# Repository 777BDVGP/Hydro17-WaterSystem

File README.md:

# Hydro17 Water System — borehole, tank, irrigation & pool controller

A home water controller on a **WEMOS LOLIN S2 Mini** (ESP32-S2): it fills a water
tank from a borehole, runs up to **9 irrigation zones** on **6 solenoid valves**,
drives the tank filter pump, and switches the **pool filter pump**, **pool light**
and a **plugs relay** on schedules. It can skip watering after rain by asking a
[Rain Gauge](https://777bdvgp.github.io/RainGauge/). Everything is a web page on
your own WiFi — no cloud, no app.

**Install / update page:** https://777bdvgp.github.io/Hydro17-WaterSystem/

**Contents:** [Features](#features) · [Hardware](#hardware) · [Pin map](#pin-map) ·
[Installing the firmware](#installing-the-firmware) · [First start: WiFi](#first-start-wifi) ·
[Rain gauge](#rain-gauge) · [Updating](#updating) ·
[Building the firmware yourself](#building-the-firmware-yourself) · [Licence](#licence)

> **Who this is for:** someone with hands-on experience in electronics and
> irrigation plumbing. It is not a kit manual. The guide grows over time —
> parts marked **(to be completed)** get more detail and photos later.

## Features

- **HOME** — live status: tank level, float switches, borehole pump, valves,
  active irrigation zone, pool pump and light, maintenance due dates.
- **Irrigation** — 9 zones, each with its own valve configuration, start date /
  time, duration, every-N-days frequency, water source (tank or borehole),
  per-weekday suspend, manual or scheduled mode; a 7-day suspend calendar.
- **Rain gauge** (optional) — asks a Rain Gauge on the same network every hour
  whether to irrigate today; zones set to "Respect Rainfall" are skipped when it
  says no. Gauge not reachable for 3 hours = irrigate as normal.
- **Tank** — fill by float switch or level sensor, any time or inside a time
  window, start / stop levels, filter pump delay after filling.
- **Pool** — filter pump 7-day schedule with manual override, pool light on / off.
- **Valves** — names for the valves and 9 valve configurations.
- **Manual operation** — switch the controller off (all automatic logic stops),
  with automatic return to normal after a set time.
- **NTFY** — free push alerts on your phone ([ntfy.sh](https://ntfy.sh)), e.g.
  maintenance due dates.
- **Reports** — general, irrigation and tank-filling logs.
- **WiFi** — saved networks list (add / delete, passwords never shown), joins the
  strongest network in range and the **strongest access point** when several
  share one WiFi name (mesh / multi-AP). Setup hotspot **Hydro17-Setup** for a new
  board or when no network can be reached.
- **ABOUT** — **firmware update from GitHub** (CHECK / INSTALL) or from an uploaded `.bin`.
- **Safety** — software watchdog, gateway keepalive ping (reboots after 5 min
  without the router), low-memory guard, optional nightly reboot.

## Hardware

- WEMOS LOLIN S2 Mini (ESP32-S2, 4 MB flash, 2 MB PSRAM).
- Main PCB: Eagle files in [`PCB/`](PCB) (`WEMOS_ESP32_2S_V5.sch` / `.brd`).
  Gerbers **(to be completed)**.
- Float / relay board: `ManualFloatRelaysV2.sch` / `.brd` and its Gerber ZIP
  [`ManualFloatRelaysV2_2024-05-08.zip`](PCB/ManualFloatRelaysV2_2024-05-08.zip).
- Relay / driver outputs for the solenoid valves, borehole pump, tank filter
  pump, pool pump, pool light and plugs; inputs for float switches and the
  panel buttons / switches; analogue tank level sensor.
- Bill of materials, wiring and photos **(to be completed)**.

## Pin map

| Output | GPIO | | Input | GPIO |
|---|---|---|---|---|
| Tank supply solenoid | 4 | | Tank level sensor (ADC) | 1 |
| Irrigation valve 1 | 5 | | Pool filter sensor (ADC) | 2 |
| Irrigation valve 2 | 6 | | Tank filter sensor (ADC) | 3 |
| Irrigation valve 3 | 7 | | Tank filter on / off button | 33 |
| Irrigation valve 4 | 8 | | Controller disable / enable button | 34 |
| Irrigation valve 5 | 9 | | Pool filter switch | 35 |
| Irrigation valve 6 | 10 | | Pool light switch | 36 |
| Borehole pump relay | 11 | | Plugs on / off switch | 37 |
| Controller disabled LED | 12 | | Tank high float switch | 38 |
| Tank low LED | 13 | | Tank low float switch | 39 |
| Tank high LED | 14 | | BOOT button (WiFi setup) | 0 |
| Pool light relay | 16 | | | |
| Pool filter pump relay | 17 | | | |
| Plugs relay | 18 | | | |
| Tank filter pump relay | 21 | | | |
| Tank fill solenoid | 40 | | | |

## Installing the firmware

No PlatformIO needed: open **https://777bdvgp.github.io/Hydro17-WaterSystem/** in
Chrome or Edge on a PC, plug the S2 Mini in with a USB **data** cable and press
**CONNECT**. Choose **Erase** for a new board, then **Install**. If no port shows
up, hold **0**, tap **RST**, release **0** and try again (tap **RST** once more
after the install).

## First start: WiFi

1. A new controller opens its own hotspot **Hydro17-Setup** (the LED blinks fast).
2. Connect a phone to it — the setup page opens by itself (otherwise browse to `http://192.168.4.1/`).
3. Pick your network, type the password and give it a **fixed IP**, press **SAVE & RESTART**.
4. Put the phone back on your WiFi and open the fixed IP (or `http://hydro17.local/`).

More networks: **SETTINGS → WiFi Networks**. Hold **BOOT** or the **CONTROLLER**
button while powering up to open the setup hotspot again. If no saved network can
be reached for about 4 minutes, the hotspot opens by itself for 5 minutes, then
the controller restarts and tries again.

## Rain gauge

On **SETTINGS** tick **Use Rain Gauge** and enter the gauge's IP (e.g.
`192.168.1.124`). The controller asks `http://<gauge>/api/irrigate` every hour (and
right after saving); the badge under the settings shows **IRRIGATE** (green) or
**NO IRRIGATION TODAY** (red). Only zones with **Respect Rainfall = Yes** are
skipped.

## Updating

On the **ABOUT** page: **CHECK FOR UPDATE** compares the version with the one on the
install page; **INSTALL FROM GITHUB** downloads and installs it (not while a zone
irrigates or the borehole pump runs). Settings and logs are kept; a failed
download leaves the old firmware running. Without internet at the controller:
download [`hydro17.bin`](docs/firmware/hydro17.bin) and use **UPLOAD & INSTALL**.

## Building the firmware yourself

[PlatformIO](https://platformio.org/) project in [`Hydro17/`](Hydro17):

```bash
cd Hydro17
pio run -e usb -t upload                                   # first flash over USB
pio run -e ota -t upload --upload-port <controller ip>     # later over WiFi
```

`main.cpp` is the single translation unit — it `#include`s every module, so every
cross-file function needs a declaration in `src/00_ForwardDecl.h`.

Optional built-in WiFi networks: copy `src/wifi_secrets.example.h` to
`src/wifi_secrets.h` (git-ignored). Builds with that file are named `_PRIVATE` —
do not share them, your passwords are inside.

## Licence

[CC BY-NC 4.0](LICENSE) — free for personal use, not for sale. No warranty: this
controls pumps, valves and pool equipment, and they run on mains power — have
mains wiring done or checked by a qualified person.

Copyright (c) 2026 Bennie Vermeulen

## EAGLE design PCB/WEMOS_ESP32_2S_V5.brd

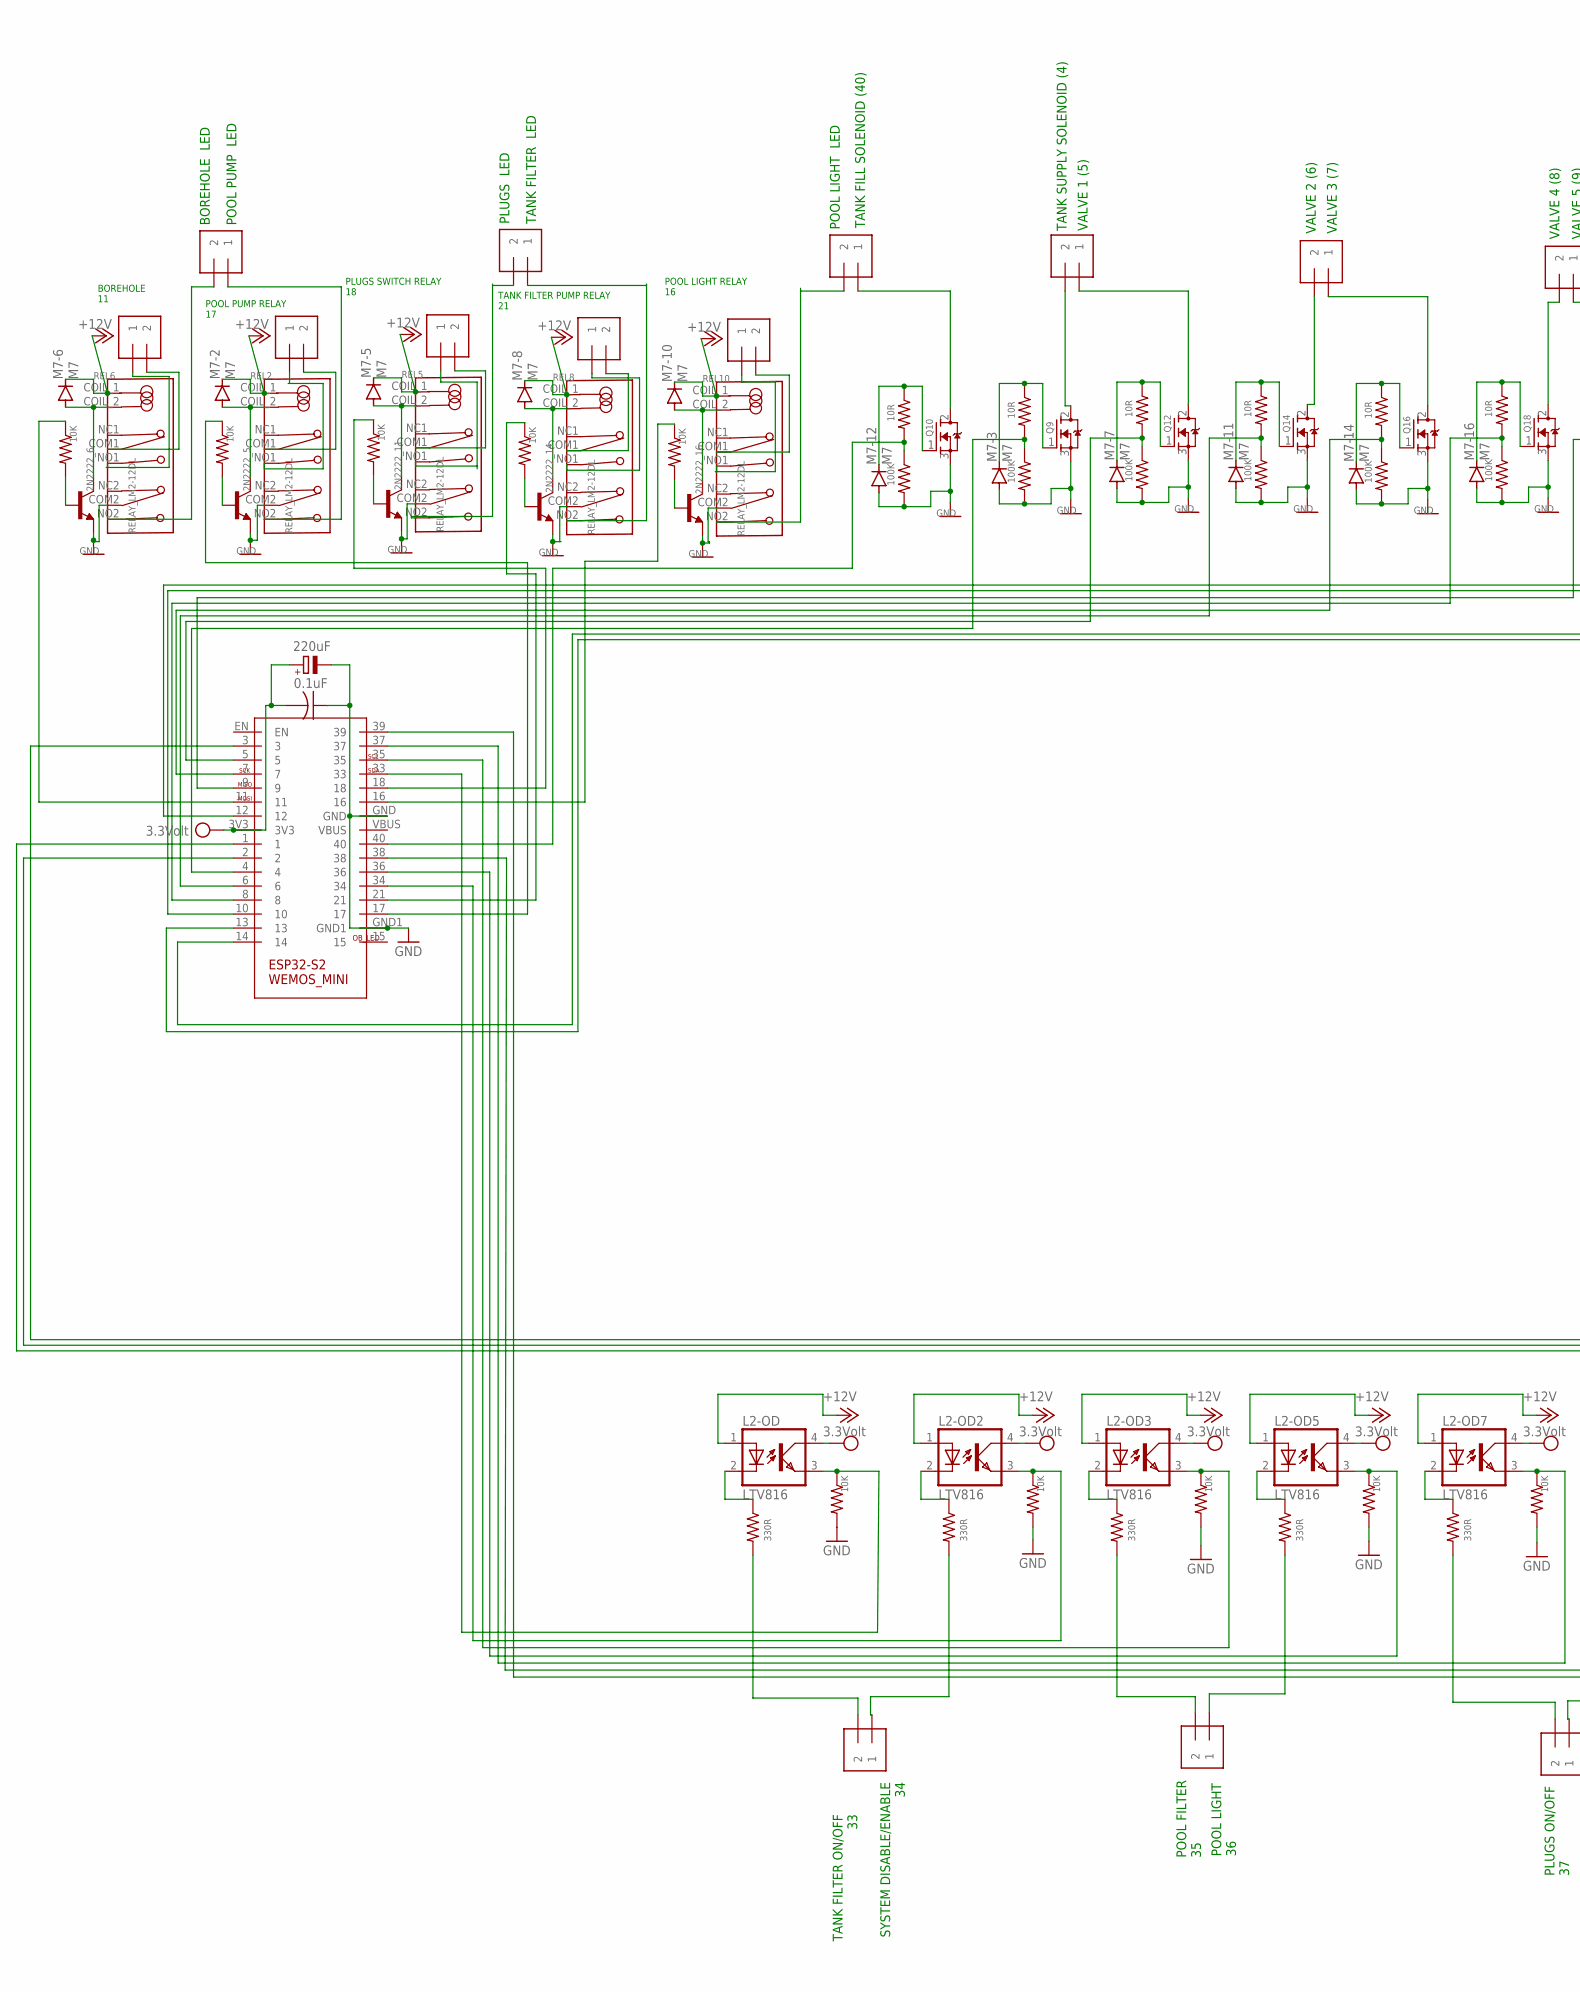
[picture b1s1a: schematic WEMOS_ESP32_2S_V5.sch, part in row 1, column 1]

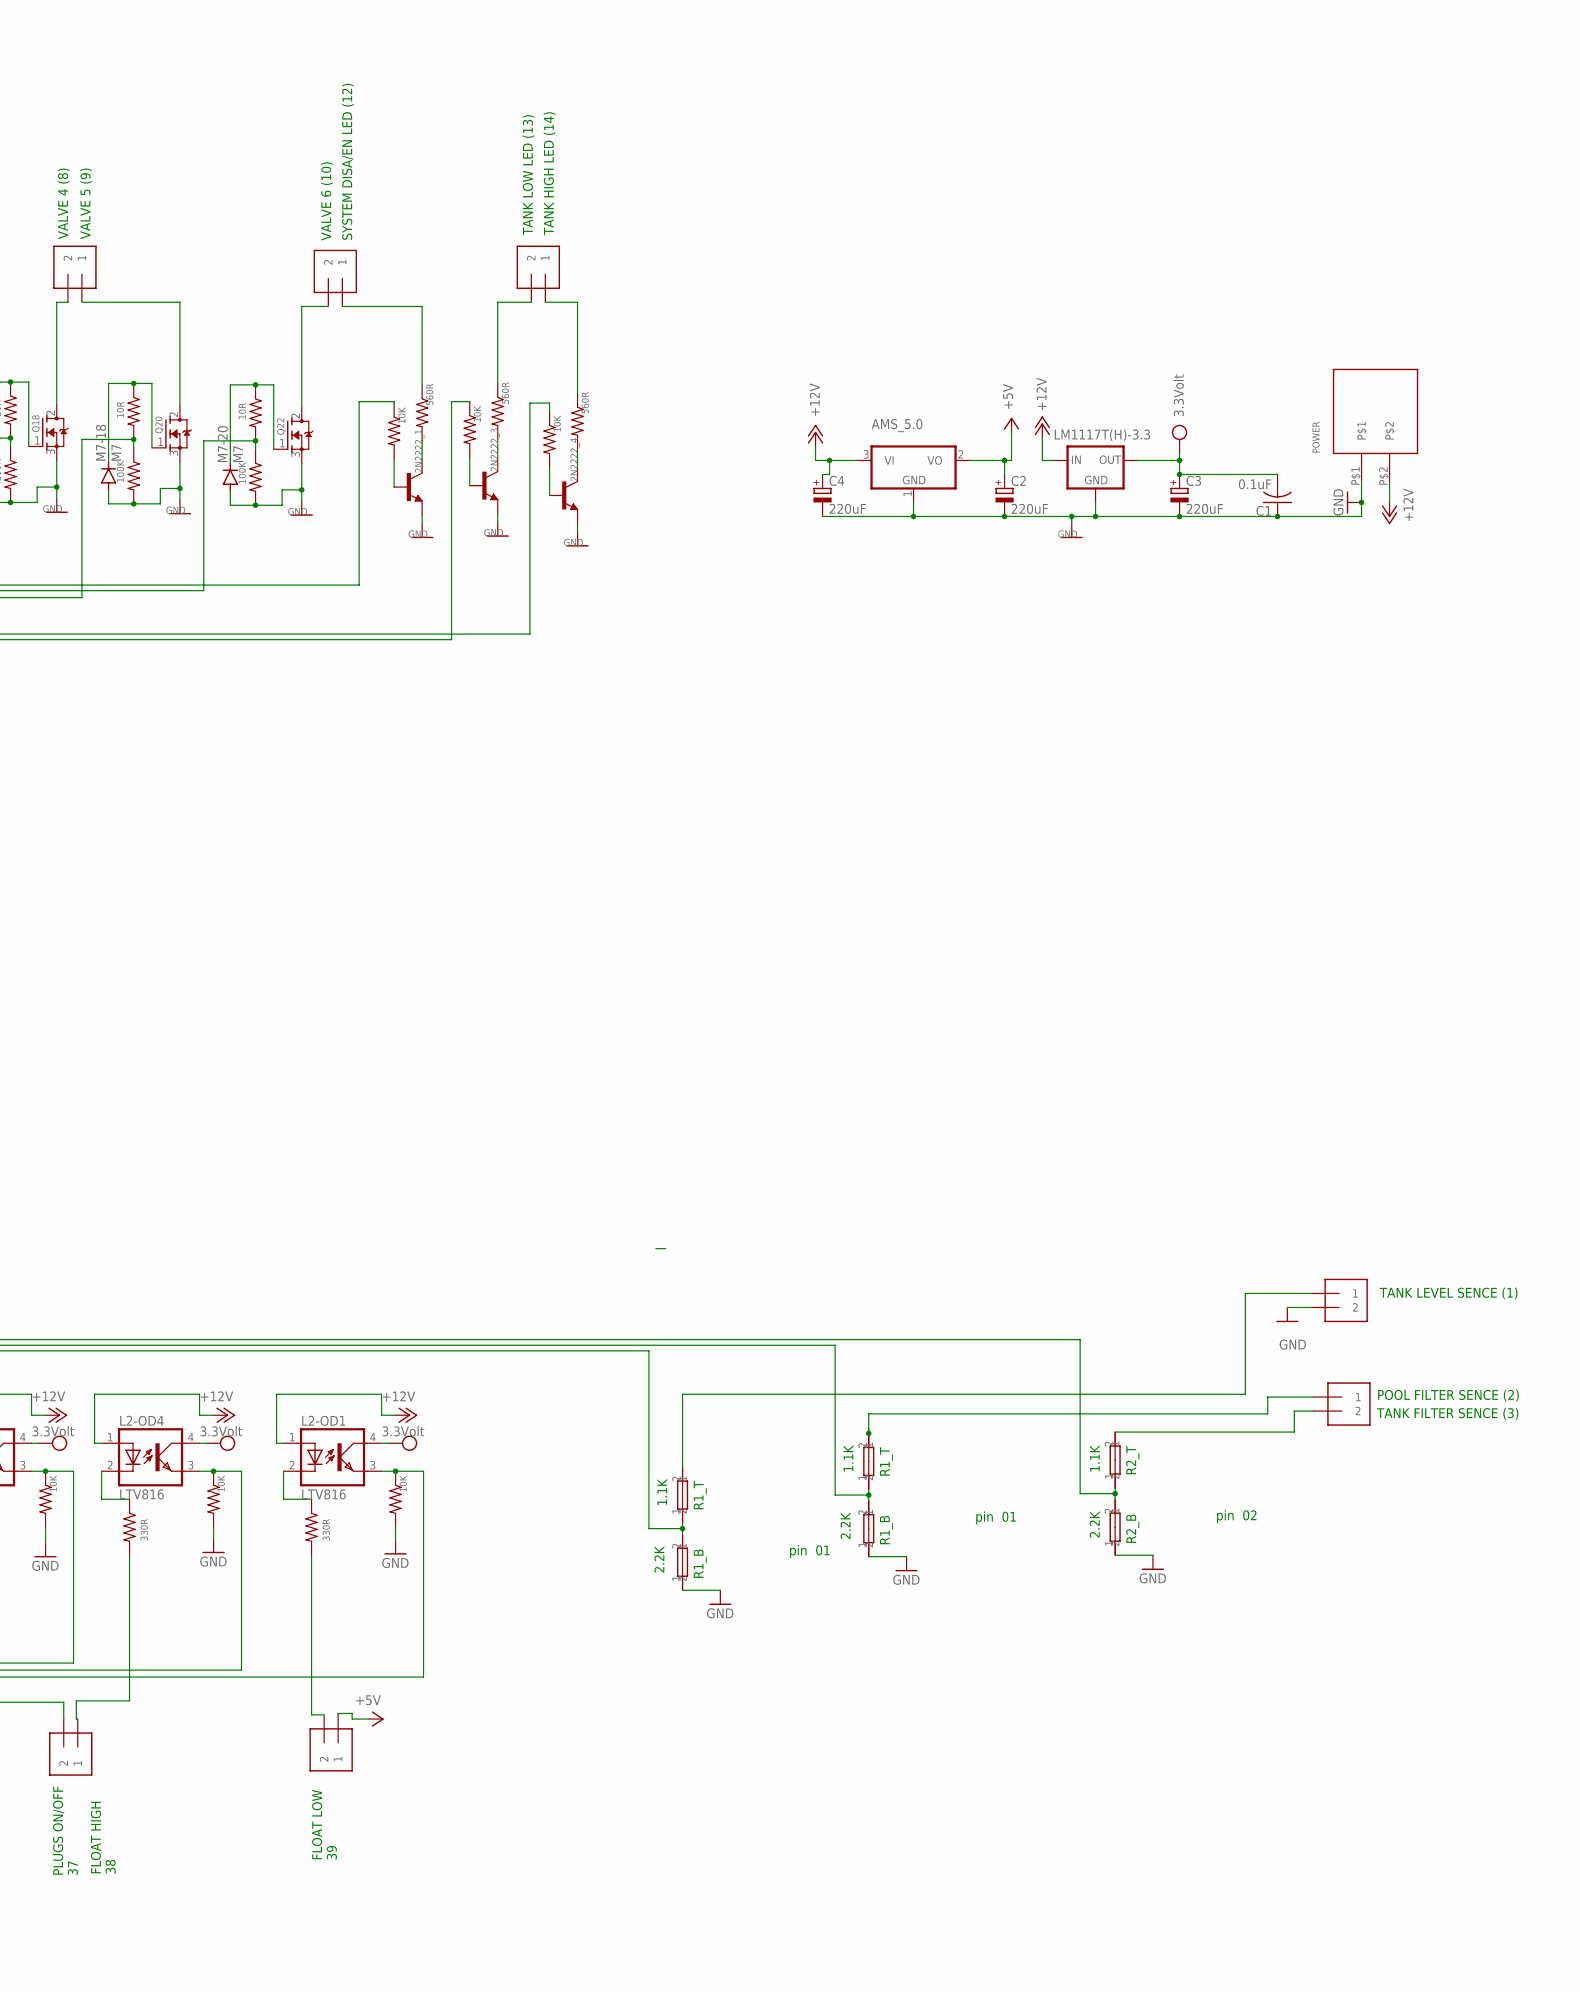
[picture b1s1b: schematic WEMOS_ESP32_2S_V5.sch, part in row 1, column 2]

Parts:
2N2222_1, 2N2222_3, 2N2222_4, 2N2222_5, 2N2222_6, 2N2222_11, 2N2222_14, 2N2222_16: 2N3904; TO92
12__1, 12__2, 12__3, 12__4, 12__5, 12__6, 12__7, 12__13, 18__1, 18__2: FLOAT; 1X2-3.5MM
+_33: AAA; 1X2-3.5MM
+_35, +_37, +_39: TERMINNAL-3.5MM-2-3.5MMDOUBLE; 1X2-3.5MM
AMS_5.0: AMS1117DB; SOT223
C1, C5: 0.1uF; C050-025X075
C2, C3, C4, C6: 220uF; E2,5-7
IC1: LM1117T(H)-3.3; TO220H
L2-OD, L2-OD1, L2-OD2, L2-OD3, L2-OD4, L2-OD5, L2-OD7: LTV816; DIL04
M7-2, M7-3, M7-5, M7-6, M7-7, M7-8, M7-10, M7-11, M7-12, M7-14, M7-16, M7-18, M7-20: M7; SOD106-R
POWER: TERMINAL-5.08MM-2BIG_HOLE; TERM-5.05-2_BH
Q9, Q10, Q12, Q14, Q16, Q18, Q20, Q22: IRF3205; TO220V
R1, R5, R7, R9, R10, R13, R15, R17, R19, R20, R21, R23, R24, R28, R30: 10K; R0805
R1_B, R1_B2: 2.2K; 0207/10
R1_B1: 2.2k; 0207/10
R1_T, R1_T1, R2_T1: 1.1K; 0207/10
R3, R12, R14, R16, R18, R22, R29: 330R; R0805
R4, R25, R31: 560R; R0805
R8, R26, R32, R36, R40, R43, R45, R50: 10R; R0805
R11, R27, R33, R37, R41, R46, R47, R51: 100K; R0805
REL2, REL5, REL6, REL8, REL10: RELAY_LM2-12DL; RELAY4078
U$1: WEMOS_S2_MINI
XX1, XX3, XX6, XX8, XX10: FLOAT; 1X2-3.5MM

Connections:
+5V: +_39.1, AMS_5.0.2 (VO), C2.+
+12V: AMS_5.0.3 (VI), C4.+, IC1.3 (IN), L2-OD.1 (A), L2-OD1.1 (A), L2-OD2.1 (A), L2-OD3.1 (A), L2-OD4.1 (A), L2-OD5.1 (A), L2-OD7.1 (A), M7-2.C, M7-5.C, M7-6.C, M7-8.C, M7-10.C, POWER.P$2, REL2.COIL_1 (COIL1), REL5.COIL_1 (COIL1), REL6.COIL_1 (COIL1), REL8.COIL_1 (COIL1), REL10.COIL_1 (COIL1)
GND: 2N2222_1.3 (E), 2N2222_3.3 (E), 2N2222_4.3 (E), 2N2222_5.3 (E), 2N2222_6.3 (E), 2N2222_11.3 (E), 2N2222_14.3 (E), 2N2222_16.3 (E), 18__1.2, AMS_5.0.1 (GND), C1.1, C2.-, C3.-, C4.-, C5.1, C6.-, IC1.1 (GND), M7-3.A, M7-7.A, M7-11.A, M7-12.A, M7-14.A, M7-16.A, M7-18.A, M7-20.A, POWER.P$1, Q9.3 (S), Q10.3 (S), Q12.3 (S), Q14.3 (S), Q16.3 (S), Q18.3 (S), Q20.3 (S), Q22.3 (S), R1_B.1, R1_B1.1, R1_B2.1, R7.2, R11.2, R13.2, R15.2, R17.2, R19.2, R23.2, R27.2, R30.2, R33.2, R37.2, R41.2, R46.2, R47.2, R51.2, REL2.COM2, REL5.COM2, REL6.COM2, REL8.COM2, REL10.COM2, U$1.GND, U$1.GND1
unnamed: R26.2, R27.1, U$1.5
unnamed: 2N2222_6.2 (B), R10.2
unnamed: +_33.2, R3.2
unnamed: R24.1, U$1.16
unnamed: L2-OD.2 (C), R3.1
unnamed: R43.2, R46.1, U$1.40
unnamed: 12__13.2, REL6.NO2
unnamed: R5.1, U$1.17
unnamed: M7-3.C, Q9.1 (G), R8.1
unnamed: R1_B1.2, R2_T1.1, U$1.3
unnamed: R8.2, R11.1, U$1.4
unnamed: 2N2222_3.2 (B), R21.2
unnamed: 2N2222_5.1 (C), M7-2.A, REL2.COIL_2 (COIL2)
unnamed: 2N2222_1.1 (C), R4.2
unnamed: 2N2222_5.2 (B), R5.2
unnamed: REL2.COM1, XX3.2
unnamed: R9.1, U$1.18
unnamed: R20.1, U$1.21
unnamed: REL2.NO1, XX3.1
unnamed: L2-OD1.2 (C), R29.1
unnamed: +_39.2, R29.2
unnamed: 2N2222_3.1 (C), R25.2
unnamed: M7-7.C, Q12.1 (G), R26.1
unnamed: R10.1, U$1.11
unnamed: R1_B.2, R1_T.1, U$1.2
unnamed: 12__13.1, REL2.NO2
unnamed: R40.2, R41.1, U$1.8
unnamed: +_33.1, R12.2
unnamed: 2N2222_4.2 (B), R28.2
unnamed: R21.1, U$1.13
unnamed: 2N2222_1.2 (B), R1.2
unnamed: 2N2222_4.1 (C), R31.2
unnamed: R28.1, U$1.14
unnamed: R36.2, R37.1, U$1.7
unnamed: L2-OD7.3 (EMIT), R23.1, U$1.37
unnamed: M7-11.C, Q14.1 (G), R32.1
unnamed: R32.2, R33.1, U$1.6
unnamed: 18__1.1, R1_T1.2
unnamed: R1.1, U$1.12
unnamed: REL5.COM1, XX6.2
unnamed: L2-OD2.3 (EMIT), R13.1, U$1.34
unnamed: L2-OD.3 (EMIT), R7.1, U$1.33
unnamed: 18__2.2, R2_T1.2
unnamed: M7-14.C, Q16.1 (G), R36.1
unnamed: REL5.NO1, XX6.1
unnamed: L2-OD1.3 (EMIT), R30.1, U$1.39
unnamed: L2-OD2.2 (C), R12.1
unnamed: REL8.COM1, XX8.2
unnamed: REL8.NO1, XX8.1
unnamed: REL10.COM1, XX10.2
unnamed: REL10.NO1, XX10.1
unnamed: M7-16.C, Q18.1 (G), R40.1
unnamed: REL6.COM1, XX1.2
unnamed: REL6.NO1, XX1.1
unnamed: +_35.2, R14.2
unnamed: L2-OD5.3 (EMIT), R19.1, U$1.36
unnamed: 18__2.1, R1_T.2
unnamed: L2-OD3.2 (C), R14.1
unnamed: +_35.1, R18.2
unnamed: L2-OD3.3 (EMIT), R15.1, U$1.35
unnamed: 2N2222_6.1 (C), M7-6.A, REL6.COIL_2 (COIL2)
unnamed: +_37.2, R22.2
unnamed: M7-18.C, Q20.1 (G), R45.1
unnamed: L2-OD4.2 (C), R16.1
unnamed: +_37.1, R16.2
unnamed: L2-OD4.3 (EMIT), R17.1, U$1.38
unnamed: R45.2, R47.1, U$1.9
unnamed: L2-OD5.2 (C), R18.1
unnamed: 2N2222_11.1 (C), M7-5.A, REL5.COIL_2 (COIL2)
unnamed: 2N2222_11.2 (B), R9.2
unnamed: M7-12.C, Q10.1 (G), R43.1
unnamed: 12__1.2, REL5.NO2
unnamed: L2-OD7.2 (C), R22.1
unnamed: M7-20.C, Q22.1 (G), R50.1
unnamed: R50.2, R51.1, U$1.10
unnamed: 12__1.1, REL8.NO2
unnamed: 12__2.2, REL10.NO2
unnamed: 2N2222_14.1 (C), M7-8.A, REL8.COIL_2 (COIL2)
unnamed: 2N2222_14.2 (B), R20.2
unnamed: 12__2.1, Q10.2 (D)
unnamed: R1_B2.2, R1_T1.1, U$1.1
unnamed: 12__3.2, Q9.2 (D)
unnamed: 12__3.1, Q12.2 (D)
unnamed: 12__4.2, Q14.2 (D)
unnamed: 2N2222_16.1 (C), M7-10.A, REL10.COIL_2 (COIL2)
unnamed: 2N2222_16.2 (B), R24.2
unnamed: 12__4.1, Q16.2 (D)
unnamed: 12__5.2, Q18.2 (D)
unnamed: 12__5.1, Q20.2 (D)
unnamed: 12__6.2, Q22.2 (D)
unnamed: 12__6.1, R4.1
unnamed: 12__7.2, R25.1
unnamed: 12__7.1, R31.1
VCC: C1.2, C3.+, C5.2, C6.+, IC1.2 (OUT), L2-OD.4 (COL), L2-OD1.4 (COL), L2-OD2.4 (COL), L2-OD3.4 (COL), L2-OD4.4 (COL), L2-OD5.4 (COL), L2-OD7.4 (COL), U$1.3V3

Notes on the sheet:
BOREHOLE 11
R1_T
R1_B
R2_T
R2_B
TANK FILTER ON/OFF 33
SYSTEM DISABLE/ENABLE 34
POOL FILTER 35
POOL LIGHT 36
PLUGS ON/OFF 37
FLOAT HIGH 38
pin 01
pin 02
1.1K
2.2K
POOL PUMP RELAY 17
PLUGS SWITCH RELAY 18
TANK FILTER PUMP RELAY 21
POOL LIGHT RELAY 16
BOREHOLE LED
POOL PUMP LED
PLUGS LED
TANK FILTER LED
POOL LIGHT LED
TANK FILL SOLENOID (40)
TANK SUPPLY SOLENOID (4)
VALVE 1 (5)
VALVE 2 (6)
VALVE 3 (7)
VALVE 4 (8)
VALVE 5 (9)
VALVE 6 (10)
SYSTEM DISA/EN LED (12)
TANK LOW LED (13)
TANK HIGH LED (14)
FLOAT LOW 39
TANK LEVEL SENCE (1)
POOL FILTER SENCE (2)
TANK FILTER SENCE (3)

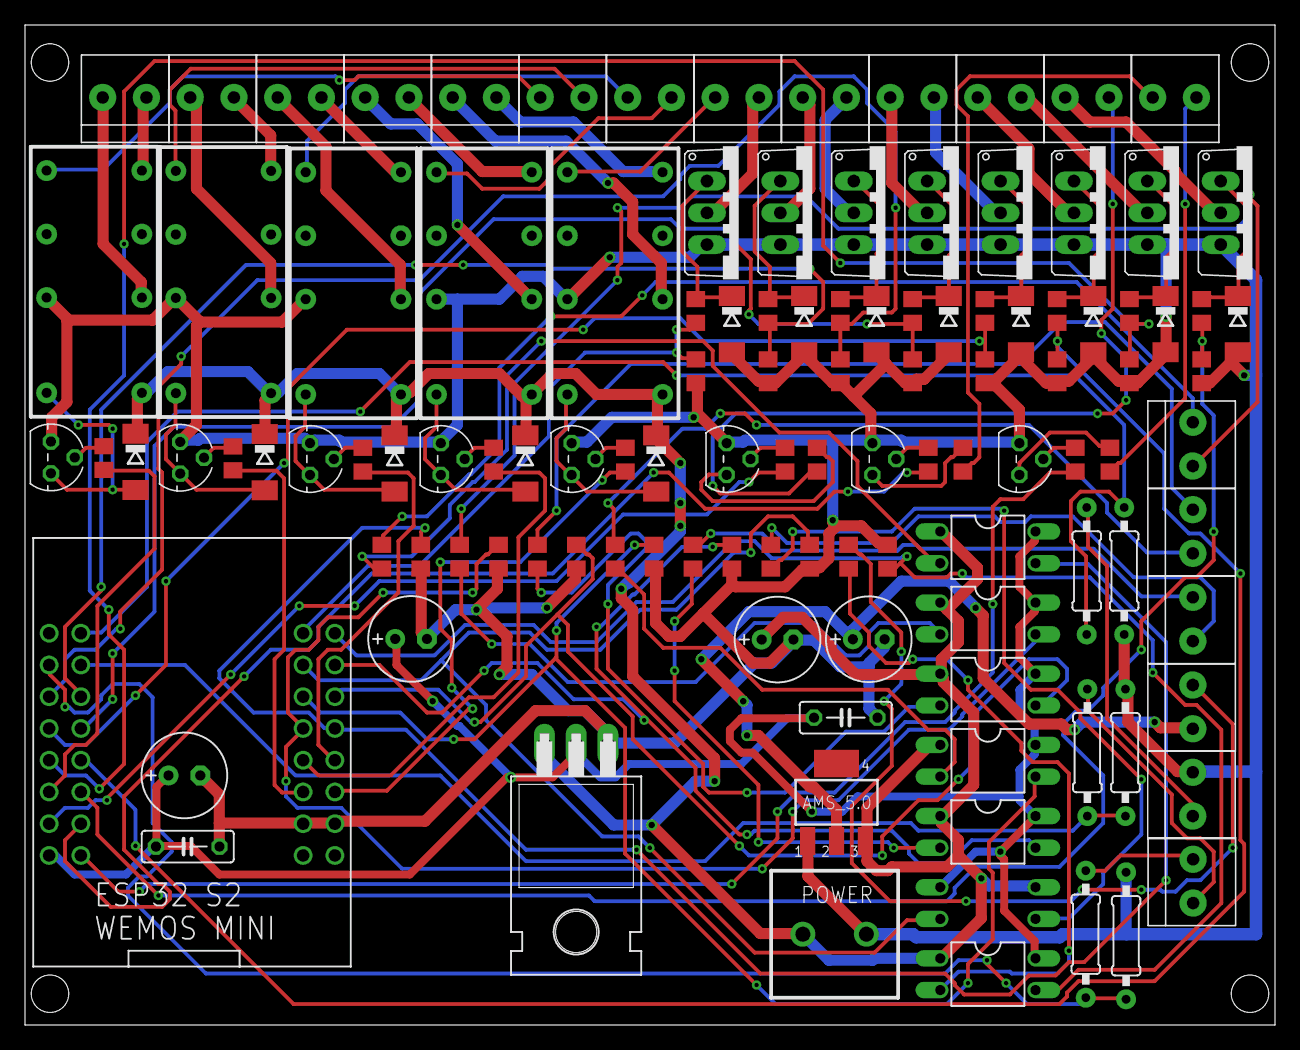
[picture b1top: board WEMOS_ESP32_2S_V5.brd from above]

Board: 2 copper layers, 100.0 x 80.0 mm, 117 parts (1 on the bottom side), 97 nets.

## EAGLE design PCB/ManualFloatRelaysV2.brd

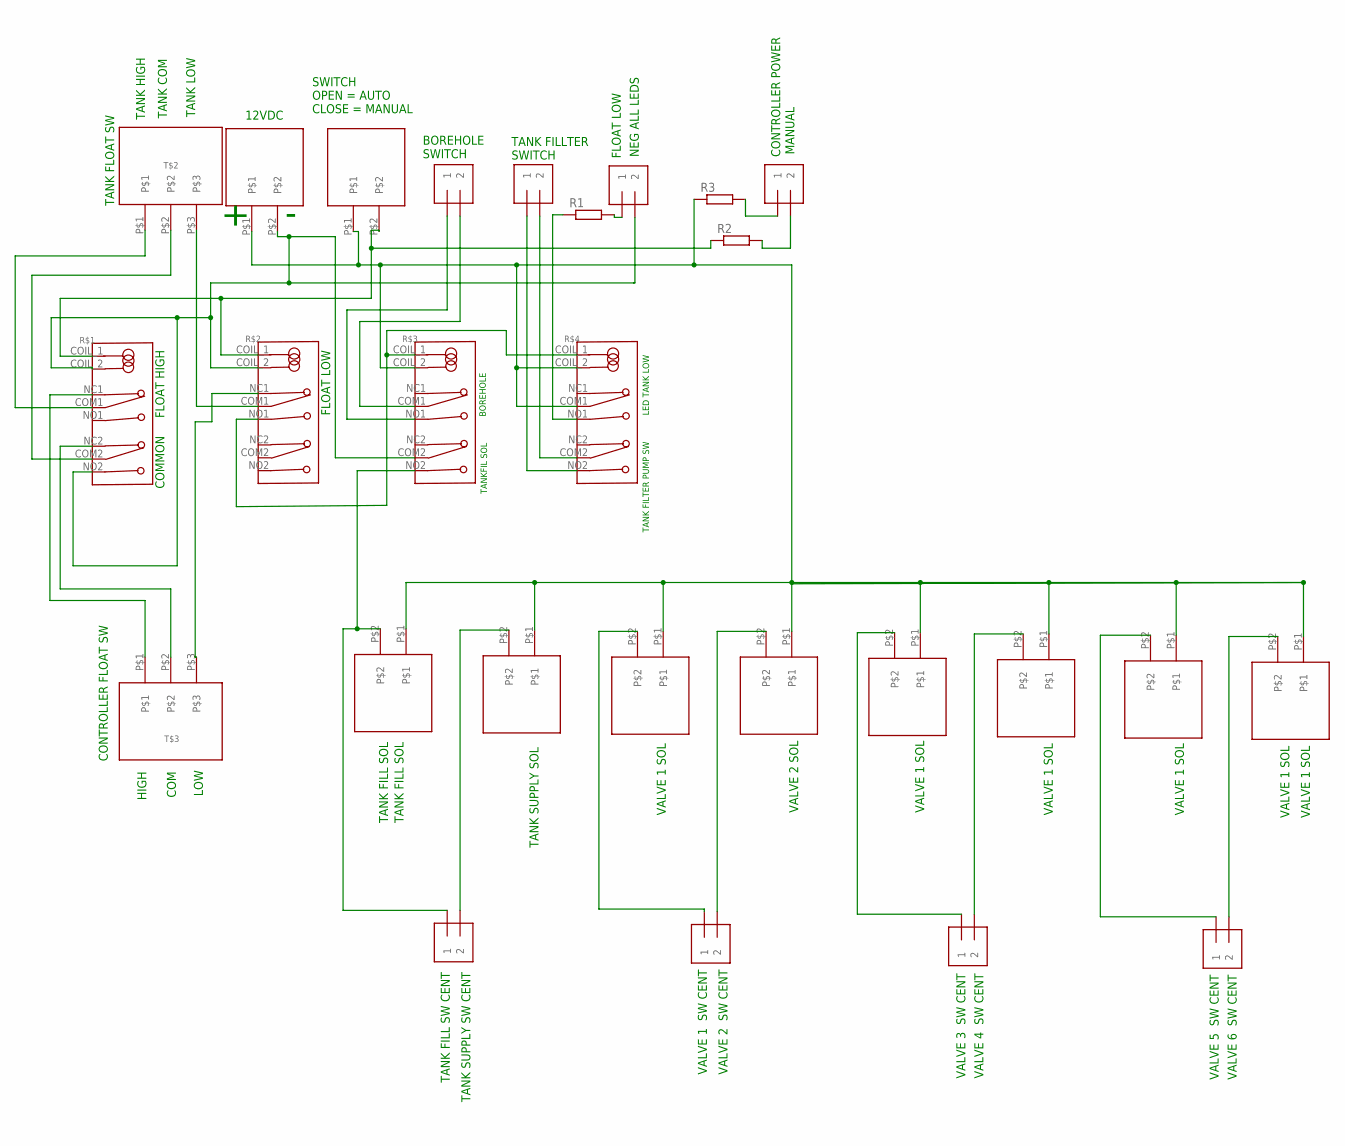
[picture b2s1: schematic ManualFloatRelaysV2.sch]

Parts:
R1, R2, R3: R-EU_0207/10; 0207/10
R$1, R$2, R$3, R$4: RELAY_LM2-12DL; RELAY4078
T$1, T$4, T$5, T$6, T$7, T$11, T$13, T$14: TERMINNAL-3.5MM-2-3.5MMDOUBLE; 1X2-3.5MM
T$2, T$3: TERMINAL-3.5MM-3TERMINAL; 1X3-3.5MM_TERM
U$1, U$2, U$3, U$4, U$5, U$6, U$7, U$8, U$9, U$10: TERMINAL-5.08MM-2BIG_HOLE; TERM-5.05-2_BH

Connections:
unnamed: R$2.NO1, R$3.COIL_1 (COIL1), R$4.COIL_1 (COIL1)
unnamed: T$11.1, U$4.P$2
unnamed: R2.1, R$1.COIL_1 (COIL1), R$2.COIL_1 (COIL1), U$10.P$2
unnamed: R$1.COIL_2 (COIL2), R$1.NO2, R$2.COIL_2 (COIL2), R$3.COM2, T$4.2, U$2.P$2
unnamed: R$1.COM1, T$2.P$1
unnamed: R$1.COM2, T$2.P$2
unnamed: R$2.COM1, T$2.P$3
unnamed: R$1.NC1, T$3.P$1
unnamed: R$1.NC2, T$3.P$2
unnamed: R$2.NC1, T$3.P$3
unnamed: R$3.NO1, T$5.1
unnamed: R$3.COM1, T$5.2
unnamed: R$3.NO2, T$7.1, U$1.P$2
unnamed: R$4.COM2, T$1.2
unnamed: T$13.1, U$5.P$2
unnamed: R$4.NO2, T$1.1
unnamed: T$7.2, U$3.P$2
unnamed: T$11.2, U$6.P$2
unnamed: R3.1, R$3.COIL_2 (COIL2), R$4.COIL_2 (COIL2), R$4.COM1, U$1.P$1, U$2.P$1, U$3.P$1, U$4.P$1, U$5.P$1, U$6.P$1, U$7.P$1, U$8.P$1, U$9.P$1, U$10.P$1
unnamed: T$13.2, U$8.P$2
unnamed: T$14.1, U$7.P$2
unnamed: T$14.2, U$9.P$2
unnamed: R1.1, R$4.NO1
unnamed: R1.2, T$4.1
unnamed: R2.2, T$6.2
unnamed: R3.2, T$6.1

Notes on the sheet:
TANK FLOAT SW
CONTROLLER FLOAT SW
SWITCH OPEN = AUTO CLOSE = MANUAL
HIGH
LOW
TANK FILLTER SWITCH
BOREHOLE SWITCH
12VDC
TANK HIGH
TANK COM
TANK LOW
COM
TANK FILL SW CENT
TANK FILL SOL
TANK SUPPLY SW CENT
TANK SUPPLY SOL
VALVE 1 SW CENT
VALVE 1 SOL
VALVE 2 SW CENT
VALVE 2 SOL
VALVE 3 SW CENT
VALVE 4 SW CENT
VALVE 5 SW CENT
VALVE 6 SW CENT
COMMON
FLOAT HIGH
FLOAT LOW
BOREHOLE
TANKFIL SOL
TANK FILTER PUMP SW
LED TANK LOW
MANUAL
CONTROLLER POWER
NEG ALL LEDS

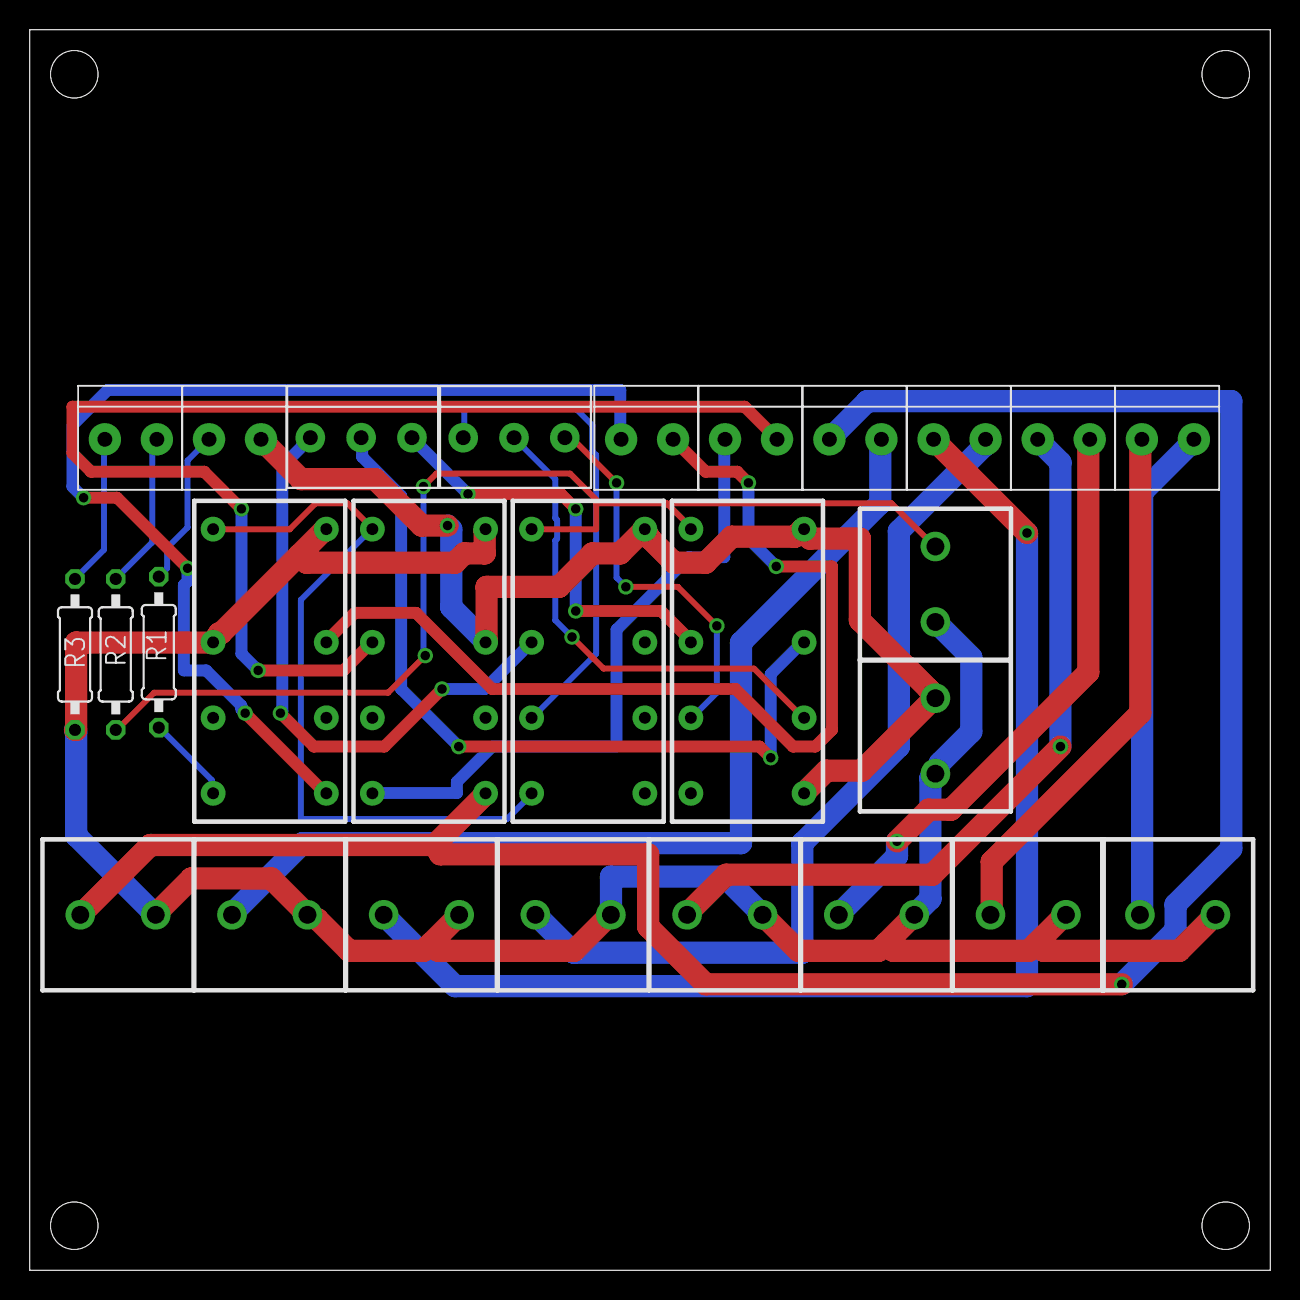
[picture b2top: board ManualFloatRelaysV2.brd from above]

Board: 2 copper layers, 83.5 x 83.5 mm, 27 parts (0 on the bottom side), 26 nets.
